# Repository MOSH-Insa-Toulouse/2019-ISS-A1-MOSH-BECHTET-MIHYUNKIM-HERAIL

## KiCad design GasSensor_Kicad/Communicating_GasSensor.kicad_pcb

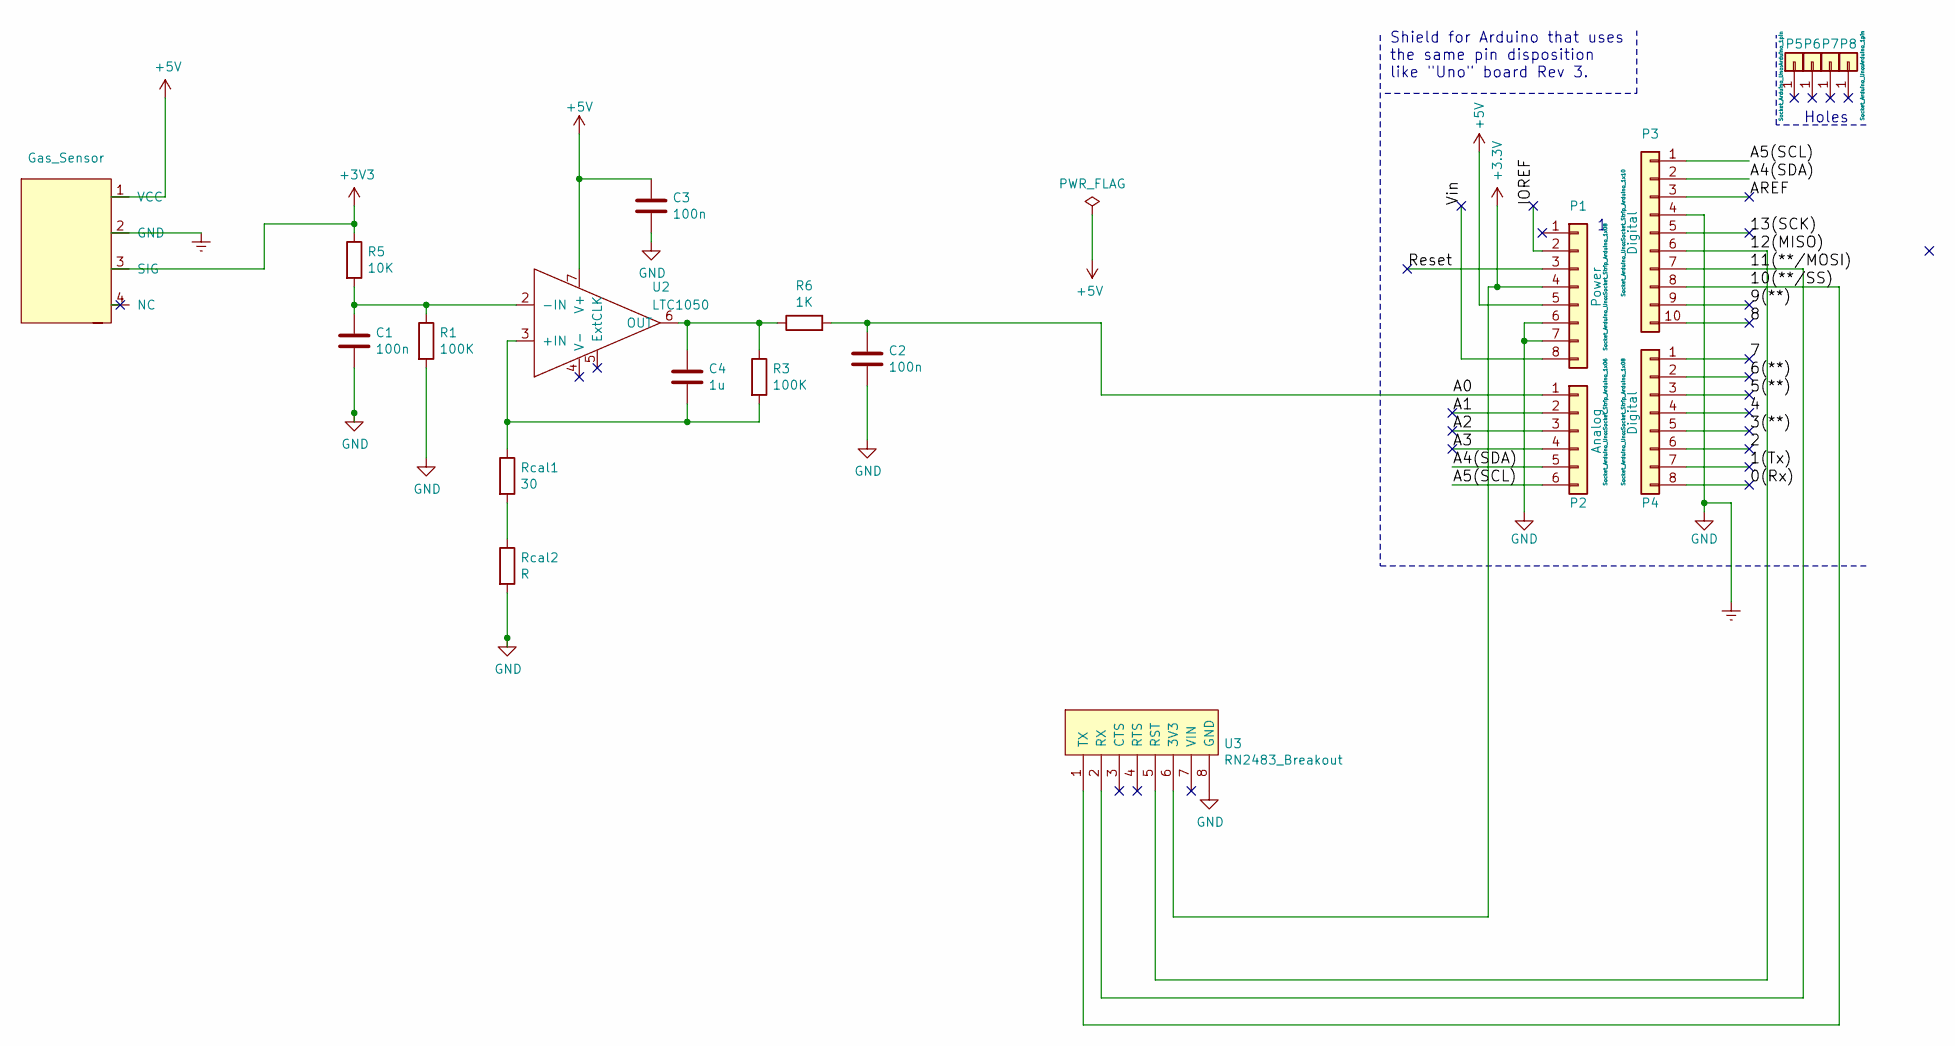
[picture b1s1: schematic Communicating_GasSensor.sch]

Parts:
C1, C2, C3: 100n; CP_Elec_4x3
C4: 1u; CP_Elec_4x3
P1: Power; Socket_Strip_Arduino_1x08
P2: Analog; Socket_Strip_Arduino_1x06
P3: Digital; Socket_Strip_Arduino_1x10
P4: Digital; Socket_Strip_Arduino_1x08
P5, P6, P7, P8: CONN_01X01; Arduino_1pin
R1, R3: 100K; R_Axial_DIN0204_L3.6mm_D1.6mm_P1.90mm_Vertical
R5: 10K; R_Axial_DIN0204_L3.6mm_D1.6mm_P1.90mm_Vertical
R6: 1K; R_Axial_DIN0204_L3.6mm_D1.6mm_P1.90mm_Vertical
Rcal1: 30; R_Axial_DIN0204_L3.6mm_D1.6mm_P1.90mm_Vertical
Rcal2: R; R_Axial_DIN0204_L3.6mm_D1.6mm_P1.90mm_Vertical
U1: Gas_Sensor; TO-5-4
U2: LTC1050; DIP-8_W7.62mm_LongPads
U3: RN2483_Breakout

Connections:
+5V: C3.1, P1.5, U1.1 (VCC), U2.7 (V+)
/0(Rx): P4.8
/1(Tx): P4.7
/2: P4.6
/3(**): P4.5
/4: P4.4
/5(**): P4.3
/6(**): P4.2
/7: P4.1
/8: P3.10
/9(**): P3.9
/10(**/SS): P3.8, U3.1 (TX)
/11(**/MOSI): P3.7, U3.2 (RX)
/12(MISO): P3.6, U3.5 (RST)
/13(SCK): P3.5
/A0: C2.1, P2.1, R6.2
/A1: P2.2
/A2: P2.3
/A3: P2.4
/A4(SDA): P2.5, P3.2
/A5(SCL): P2.6, P3.1
/AREF: P3.3
/IOREF: P1.2
/Reset: P1.3
/Vin: P1.8
Earth: C1.2, C2.2, C3.2, P1.6, P1.7, P3.4, R1.2, Rcal2.2, U1.2 (GND), U3.8 (GND)
unnamed: C1.1, R1.1, R5.2, U2.2 (-IN)
unnamed: C4.1, R3.1, R6.1, U2.6 (OUT)
unnamed: C4.2, R3.2, Rcal1.1, U2.3 (+IN)
unnamed: Rcal1.2, Rcal2.1

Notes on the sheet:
Holes
Shield for Arduino that uses the same pin disposition like "Uno" board Rev 3.

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
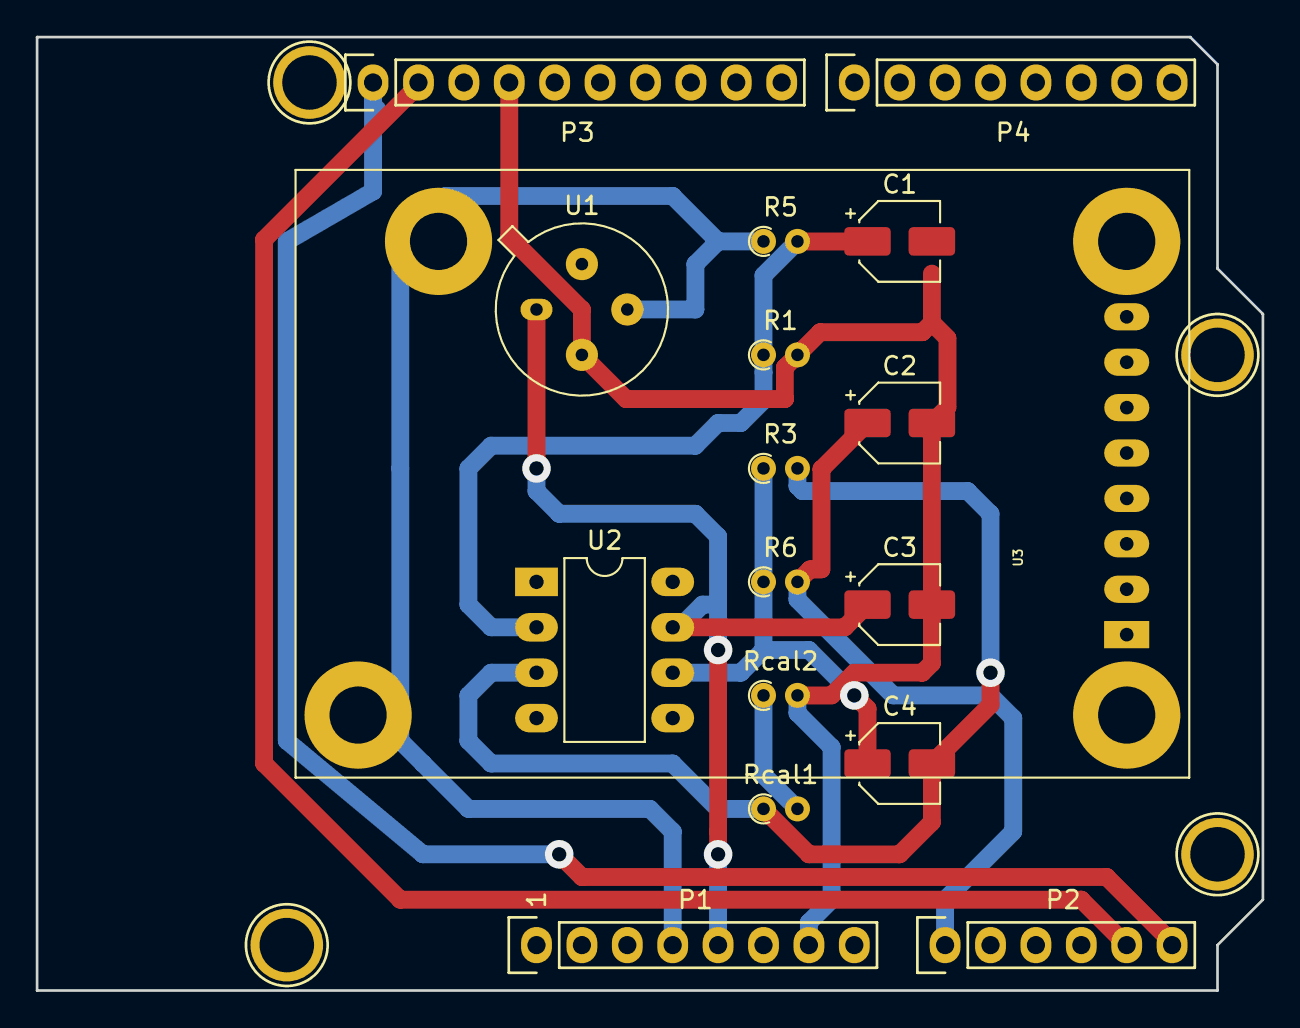
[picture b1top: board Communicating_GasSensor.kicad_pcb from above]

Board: 2 copper layers, 68.6 x 53.3 mm, 21 parts (0 on the bottom side), 13 nets.

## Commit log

2019-11-18 lib + small modifs
2019-11-18 with the test for gas sensor
2019-11-18 stuff
2019-11-18 basic interrupt
2019-11-18 some stuff to test
2019-11-18 Some fixes, still to be tested
2019-11-18 format
2019-11-18 more format
2019-11-18 removed a command
2019-11-18 comments
2019-11-18 More comments
2019-11-19 Interrupt + sleep working basic
2019-11-20 node red flow
2019-11-25 Measures with first
2020-01-22 message
